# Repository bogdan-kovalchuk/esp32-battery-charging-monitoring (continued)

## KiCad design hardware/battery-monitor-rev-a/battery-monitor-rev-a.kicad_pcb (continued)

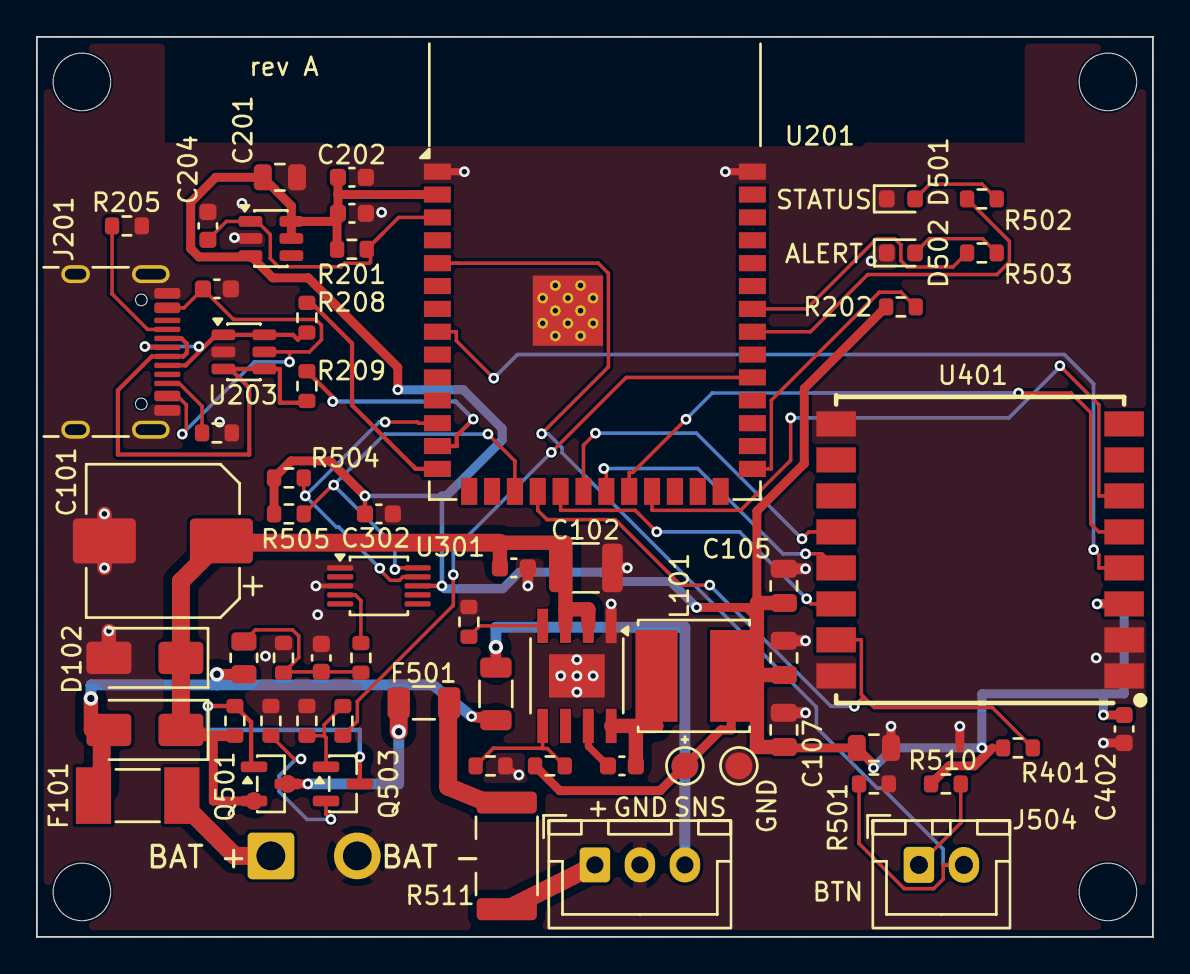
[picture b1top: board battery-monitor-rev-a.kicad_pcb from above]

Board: 4 copper layers, 62.0 x 50.0 mm, 66 parts (0 on the bottom side), 43 nets.

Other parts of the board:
H1, H2, H3, H4: M3; MountingHole_3.2mm_M3

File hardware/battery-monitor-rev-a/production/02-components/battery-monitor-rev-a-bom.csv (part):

"Reference","Value","Footprint","MPN","Manufacturer","Quantity","Population","Note"
"C101","22uF 100V","Capacitor_SMD:CP_Elec_8x10","EEE-FK2A220P","Panasonic","1","","damping of hot-plug ringing on battery leads (PWR-020); aluminium SMD 8x10"
"C102","10uF 100V","Capacitor_SMD:C_1210_3225Metric","GRM32EC72A106KE05L","Murata","1","","10 uF 100 V X7S 1210; 4.32 uF effective at 31 V (Murata curve, c102-choice.md); TI 4.7 uF effective minimum met up to 28.4 V, C101 in parallel"
"C103","100nF 100V","Capacitor_SMD:C_0603_1608Metric","CL10B104KC8NNNC","Samsung","1","","X7R 100 V, next to U101 VIN/GND"
"C104,C202-C205,C301,C302,C402","100nF","Capacitor_SMD:C_0603_1608Metric","CL10B104KB8NNNC","Samsung","8","","RC with 9.57k source: tau 0.96 ms, 16-bit settling 11 tau = 11 ms,U301 VDD decoupling,bootstrap, >= 16 V"
"C105-C107,C201","22uF","Capacitor_SMD:C_0805_2012Metric","GRM21BR61E226ME44L","Murata","4","",""
"C401","10uF","Capacitor_SMD:C_0805_2012Metric","CL21A106KAYNNNE","Samsung","1","",""
"D101","B1100","Diode_SMD:D_SMA","B1100-13-F","Diodes Incorporated","1","","reverse-polarity block, 100 V 1 A SMA; VF 0.79 V max at 1 A (Diodes DS30018); was MCC SS110-LTP (2026-10-25 IMRAD-stock change); do not substitute a 60 V SS1x family part"
"D102","SMAJ33A","Diode_SMD:D_SMA","SMAJ33A-TR","STMicroelectronics","1","","owner Q1: 24 V systems -> SMAJ33A (VWM 33 V, VC 53.3 V at 7.5 A < 85 V U101); documented 48 V alternate only: SMAJ58A/SMAJ64A; pad 1 = cathode band to VIN_PROT"
"D501","GREEN","LED_SMD:LED_0603_1608Metric","LTST-C191KGKT","Lite-On","1","","STATUS (GPIO40): Wi-Fi/report state; yellow-green 571 nm, VF 2.0 V typ / 2.4 V max at 20 mA (Lite-On LTST-C191KGKT, 2026-10-25, was Foryard FYLS-0603GD): about 1.3 mA from GPIO40 via R502 1k; 3 V emerald-green LEDs stay dim or dark"
"D502","RED","LED_SMD:LED_0603_1608Metric","KP-1608SURCK","Kingbright","1","","ALERT (GPIO41): battery critical; 630 nm, VF 1.95 V typ / 2.5 V max (Kingbright KP-1608SURCK, 2026-10-25, was Hubei KENTO KT-0603R)"
"F101","2A 125V","Fuse:Fuse_Littelfuse-NANO2-451_453","0451002.MRL","Littelfuse","1","","2 A 125 V very fast NANO2 451 (IMRAD-stock change 2026-10-25, was 0466002.NRHF 1206): interrupting 50 A at 125 V AC/DC, 300 A at 32 V DC; cold 0.0367 ohm; melting I2t 0.530 A2s, hot-plug inrush about 0.04 A2s = 7.5 %; still clears a shorted D102"
"F501","0.25A 125V","Fuse:Fuse_1206_3216Metric","0466.250NRHF","Littelfuse","1","","gauge fault fuse (review R2-01): cold 0.710 ohm, melting I2t 0.0010 A2s, 300 % <= 0.2 s, 200 % <= 5 s (Littelfuse 466 Rev. 12/19/13); coordination table in schematic-review.md"
"J101","BAT","Connector_Wire:SolderWire-0.75sqmm_1x02_P4.8mm_D1.25mm_OD2.3mm","","","1","","solder pads for the XT30 lead; + = pin 1"
"J201","USB4105-GF-A","Connector_USB:USB_C_Receptacle_HRO_TYPE-C-31-M-12","USB4105-GF-A","GCT","1","","data and programming only; VBUS does not power the board; GCT USB4105-GF-A on the HRO TYPE-C-31-M-12 land (2026-10-25, HRO not stocked in Ukraine): signal pads identical, VBUS/GND 0.05 mm shift, shell legs 0.80/1.10 mm in the 1.2/1.7 mm slots; test-fit on a bare board before soldering"
"J503","VOLTMETER","Connector_JST:JST_XH_B3B-XH-A_1x03_P2.50mm_Vertical","B3B-XH-A(LF)(SN)","JST","1","","0.28 in LED voltmeter 0-100 V: 1 V_GAUGE (module supply, 4-30 V), 2 GND, 3 SENSE via R512 10k from VBAT_FUSED; 2-wire module: pins 1-2, pin 3 unused"
"J504","BTN_EXT","Connector_JST:JST_XH_B2B-XH-A_1x02_P2.50mm_Vertical","B2B-XH-A(LF)(SN)","JST","1","Populated","External wake button (active high): 1 BTN_PULL (+3V3 via R510 1k), 2 BTN_USER (GPIO5, R501 10k pull-down to GND)"
"L101","22uH","Inductor_SMD:L_Bourns_SRN6045TA","SRN6045-220M","Bourns","1","","22 uH, ripple 0.34-0.36 A at 32-62 V in; SRN6045-220M (2026-10-25, was SRN6045TA-220M Isat 2.5 A): DCR 0.142 ohm max, Irms 1.5 A, Isat 1.9 A (L -30 %), above the LMR38010 1.6 A typ limit; same footprint; Sumida CDRH6D38NP-220NC (IMRAD) rejected: 1.3 A rated"
"Q501","SI2309CDS","Package_TO_SOT_SMD:SOT-23","SI2309CDS-T1-GE3","Vishay Siliconix","1","","gauge high-side switch (W23: single P-MOS): source on VIN_PROT (after D101, reverse-safe), drain to GAUGE_SW; -60 V, VGS(th) -1..-3 V; pulsed ID -8 A (10 us)"
"Q503","MMBT5551","Package_TO_SOT_SMD:SOT-23","MMBT5551LT1G","onsemi","1","","160 V NPN current sink for the gauge switch gate"
"R101","68k","Resistor_SMD:R_0603_1608Metric","RC0603FR-0768KL","Yageo","1","","RT: fSW = (30970/68)^(1/1.027) = 388 kHz (SNVSC73B eq. 2); full regulation to 65 V at tON-MIN 131 ns"
"R102","510k","Resistor_SMD:R_0603_1608Metric","0603SAF5103T5E","Royal Ohm","1","","RFBT; Vout = 1.0 V x (1 + 510/220) = 3.318 V; +3V3 band 3.22-3.45 V (typ 3.32 V; LMR38010 PFM regulation and 1 % resistors)"
"R103","220k","Resistor_SMD:R_0603_1608Metric","RC0603FR-07220KL","Yageo","1","","RFBB; divider current 4.5 uA"
"R201,R202,R401,R501,R507","10k","Resistor_SMD:R_0603_1608Metric","0603SAF1002T5E","Royal Ohm","5","","emitter: Ic = 70-105 uA,pull-down replaces the DevKit external pull-down on GPIO34; GPIO5 has no pull at reset"
"R205,R206","5.1k","Resistor_SMD:R_0603_1608Metric","RC0603FR-075K1L","Yageo","2","",""
"R208,R209","22","Resistor_SMD:R_0603_1608Metric","RC0603FR-0722RL","Yageo","2","",""
"R304","220k 0.1%","Resistor_SMD:R_0805_2012Metric","ERA-6AEB224V","Panasonic","1","","thin film 0.1 % 25 ppm/K, 150 V; divider ratio 23.0 (0-69 V -> 0-3.0 V); always on from VBAT_FUSED (W23), 0.1 mA at 24 V"
"R305","10k 0.1%","Resistor_SMD:R_0603_1608Metric","RT0603BRD0710KL","Yageo","1","","thin film 0.1 % 25 ppm/K"
"R307,R502,R503,R510","1k","Resistor_SMD:R_0603_1608Metric","RC0603FR-071KL","Yageo","4","","AIN0 series: limits clamp current on reversal/overvoltage; source 10.6k: load error 0.18-0.39 % (typical ADS1115 input impedance), removed by the one-point calibration,button supply: pressed level 3.0 V (10k/11k), limits current to 3.3 mA when GPIO5 is driven low (power-up glitch)"
"R504,R505","4.7k","Resistor_SMD:R_0603_1608Metric","0603SAF4701T5E","Royal Ohm","2","","I2C SCL pull-up,I2C SDA pull-up"
"R506,R508,R509","100k","Resistor_SMD:R_0603_1608Metric","AC0603FR-07100KL","Yageo","3","","base pull-down: gauge off while GPIO38 floats at reset/boot,base resistor GPIO38 -> Q503, 1:2 divider with R508,gate to source (VIN_PROT): VGS = 100k x 70-105 uA = 7-10.5 V, limited to VIN_PROT at a low battery"
"R511","4.7 2512 1W","Resistor_SMD:R_2512_6332Metric","RC2512JK-074R7L","Yageo","1","","gauge short-circuit limiter (review R2-01): 2512 1 W thick film (2026-10-25 IMRAD-stock change, was Panasonic ERJ-P08J4R7V 1206 anti-surge 2.64 W / 5 s): short-time overload 2.5 x rated voltage for 5 s (Yageo RC2512, IEC 60115-1 4.13) = 5.42 V, 6.25 W, 31 J; partial-short case 1.8 W for <= 5 s = 8.9 J; dead short <= 0.78 J; ROHM ESR18 rejected: overload test 2.5 x Vr for 2 s only"
"R512","10k","Resistor_SMD:R_1206_3216Metric","1206S4F1002T5E","Royal Ohm","1","","voltmeter SENSE (J503 pin 3) from VBAT_FUSED: module reads the battery without the D101 drop; limits a sense-lead short to 3.1 mA (96 mW at 31 V; 1206 0.25 W)"
"TP102","+3V3","TestPoint:TestPoint_Pad_D1.5mm","","","1","",""
"TP103","GND","TestPoint:TestPoint_Pad_D1.5mm","","","1","",""
"U101","LMR38010SDDAR","Package_SO:TI_SO-PowerPAD-8","LMR38010SDDAR","Texas Instruments","1","","PFM + spread spectrum variant: Iq 40 uA, shutdown 3 uA; 4.2-80 V in (85 V abs max), 1 A; do not substitute FDDAR/FSDDAR (forced PWM); DDA0008B = KiCad TI_SO-PowerPAD-8"
"U201","ESP32-S3-WROOM-1-N16R8","RF_Module:ESP32-S3-WROOM-1","ESP32-S3-WROOM-1-N16R8 (or -N16 / -N8, same footprint)","Espressif","1","","owner stock N16R8; PSRAM not initialised by the firmware; N16R8 ambient -40..+65 C (indoor/garage OK)"
"U202","TPS3808G33DBVR","Package_TO_SOT_SMD:SOT-23-6","TPS3808G33DBVR","Texas Instruments","1","",""
"U203","USBLC6-2SC6","Package_TO_SOT_SMD:SOT-23-6","USBLC6-2SC6","STMicroelectronics","1","",""
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
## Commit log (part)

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2025-02-23 remove extra files
2025-02-23 reorganise some files
2025-02-23 rename flask server file
2025-02-24 change voltage pin
2025-02-24 changed approach to voltage calculation
2025-02-25 changing pins and some minor changes
2025-02-26 only send critical messages if voltage is below critical
2025-02-28 added conversion to milliseconds
2025-02-28 change some naming and vars
2025-02-28 added HTTP server and parameters
2025-02-28 adding some changes to config and wifi connection handling
2025-02-28 adding config reset and some minore changes
2025-02-28 changing AP mode
2025-03-01 some minor changes of naming
2025-03-01 minor change to handle root
2025-03-01 added UTF8 handling and some minor changes
2025-03-01 renaming serverUrl to serverIP
2025-03-01 some minor changes
2025-03-02 refactoring / updating config handling
2025-03-02 changing voltmeter on time
2025-03-02 minor changes to voltmeter on
2025-03-03 round battery voltage
2025-03-04 change message display
2025-03-04 not sending message when voltage is equal zero
2025-03-05 hide password
2025-03-05 change AP mode name
2025-03-05 not send messages with zero voltage
2025-03-05 not show password in terminal
